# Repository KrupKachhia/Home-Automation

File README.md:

# Home-Automation
The Simple Home Automation System and Door Lock System

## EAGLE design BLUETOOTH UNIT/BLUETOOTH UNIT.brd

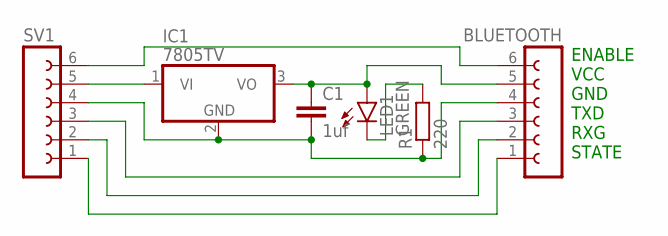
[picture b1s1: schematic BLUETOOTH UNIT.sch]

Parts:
BLUETOOTH: FE06-1; FE06
C1: 1uf; C025-025X050
IC1: 7805TV; TO220V
LED1: GREEN; SML0805
R1: 220; 0204/7
SV1: FE06-1; FE06

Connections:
unnamed: IC1.1 (VI), SV1.5
unnamed: BLUETOOTH.4, C1.2, IC1.2 (GND), R1.1, SV1.4
unnamed: BLUETOOTH.5, C1.1, IC1.3 (VO), LED1.A
unnamed: LED1.C, R1.2
unnamed: BLUETOOTH.3, SV1.3
unnamed: BLUETOOTH.6, SV1.6
unnamed: BLUETOOTH.2, SV1.2
unnamed: BLUETOOTH.1, SV1.1

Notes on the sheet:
ENABLE VCC GND TXD RXG STATE

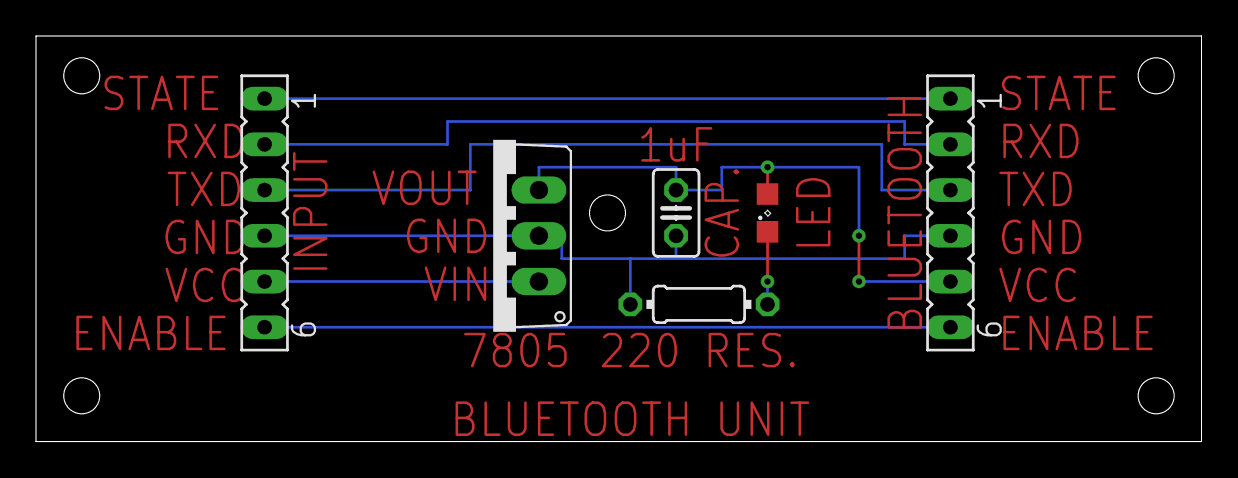
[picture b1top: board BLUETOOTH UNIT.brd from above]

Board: 2 copper layers, 64.8 x 22.5 mm, 6 parts (0 on the bottom side), 8 nets.

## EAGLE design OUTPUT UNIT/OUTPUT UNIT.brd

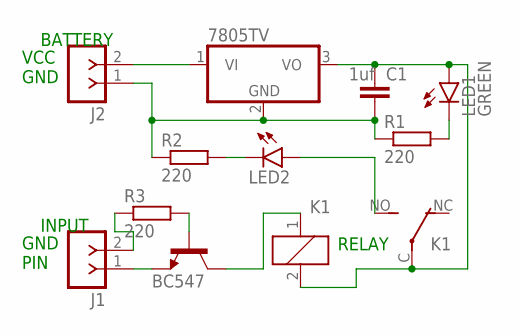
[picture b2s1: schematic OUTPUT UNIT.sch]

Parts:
C1: 1uf; C025-025X050
IC1: 7805TV; TO220V
J1, J2: F-1X02-SIP-100-32Y; SIP-100-02-32Y
K1: CQ1-12V; CQ1
LED1: GREEN; SML1206
LED2: RED; LED5MM
R1, R2, R3: 220; 0204/7
T1: BC547; TO92

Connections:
unnamed: IC1.1 (VI), J2.2
unnamed: J1.1, T1.1 (E)
unnamed: LED1.C, R1.2
unnamed: J1.2, R3.1
unnamed: C1.1, IC1.3 (VO), K1.2, K1.C, LED1.A
unnamed: C1.2, IC1.2 (GND), J2.1, R1.1, R2.1
unnamed: LED2.K (C), R2.2
unnamed: K1.NO (S), LED2.A
unnamed: K1.1, T1.3 (C)
unnamed: R3.2, T1.2 (B)

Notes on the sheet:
BATTERY
INPUT
RELAY
VCC GND
GND PIN

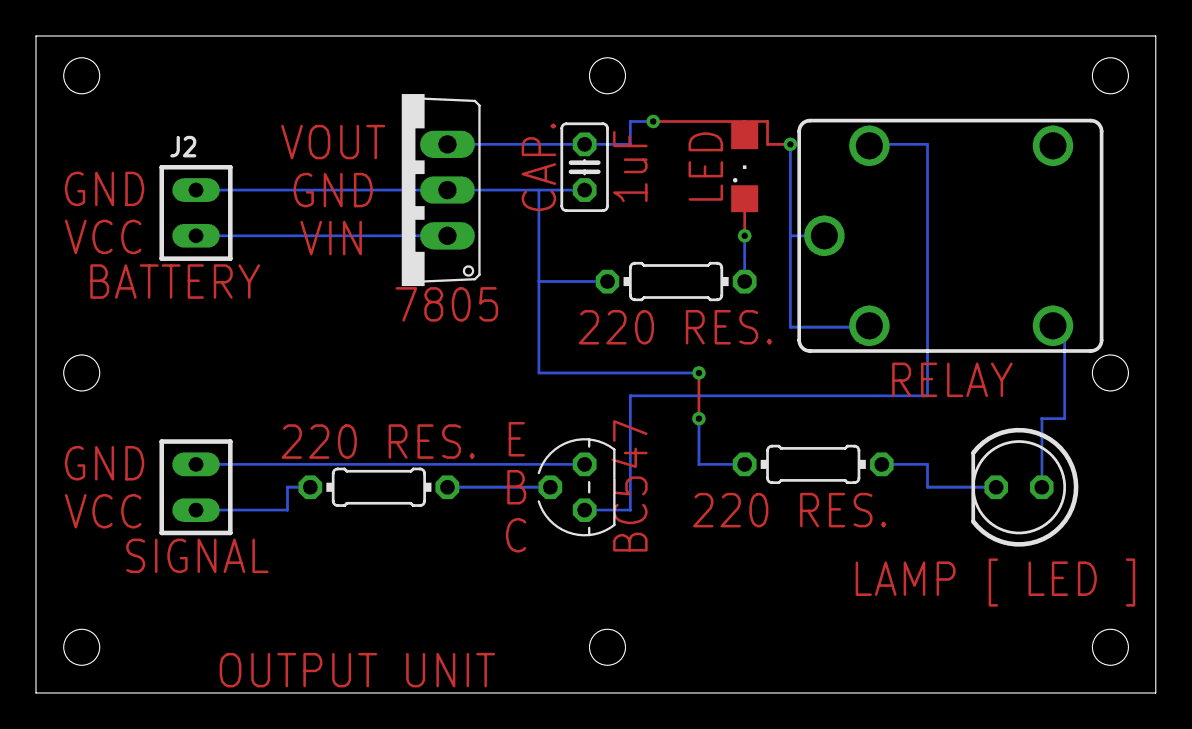
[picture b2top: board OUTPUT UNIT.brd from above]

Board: 2 copper layers, 62.2 x 36.5 mm, 11 parts (0 on the bottom side), 10 nets.

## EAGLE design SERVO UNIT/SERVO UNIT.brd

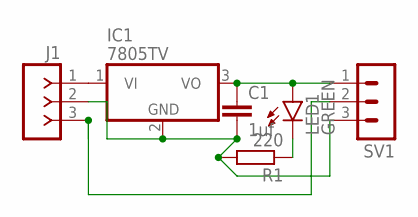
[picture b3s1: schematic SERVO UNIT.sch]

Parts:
C1: 1uf; C025-025X050
IC1: 7805TV; TO220V
J1: F-1X03-SIP-100-32Y; SIP-100-03-32Y
LED1: GREEN; SML0805
R1: 220; 0204/7
SV1: MA03-1

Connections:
unnamed: IC1.1 (VI), J1.1
unnamed: C1.1, IC1.3 (VO), LED1.A, SV1.1
unnamed: LED1.C, R1.1
unnamed: C1.2, IC1.2 (GND), J1.2, R1.2, SV1.3
unnamed: J1.3, SV1.2

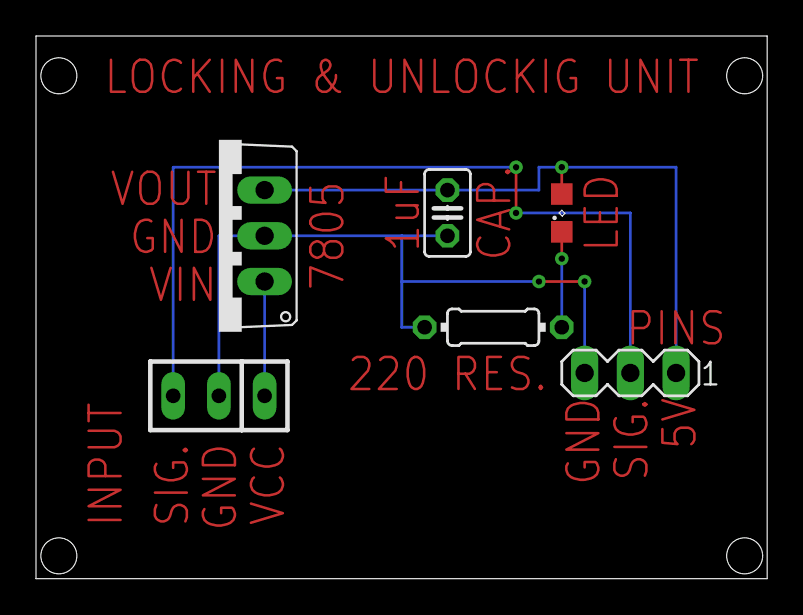
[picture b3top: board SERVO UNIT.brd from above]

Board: 2 copper layers, 40.6 x 30.2 mm, 6 parts (0 on the bottom side), 5 nets.

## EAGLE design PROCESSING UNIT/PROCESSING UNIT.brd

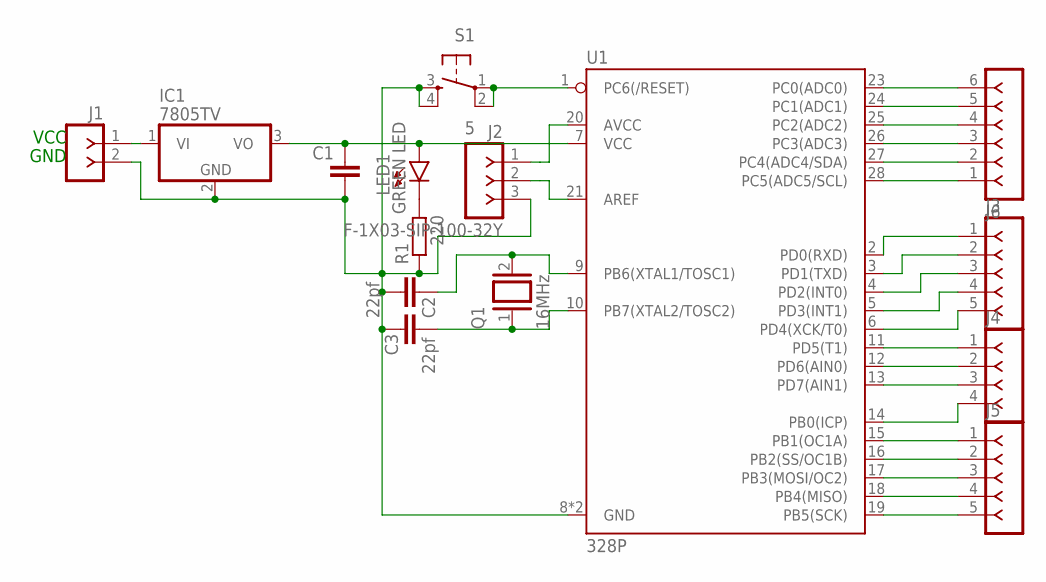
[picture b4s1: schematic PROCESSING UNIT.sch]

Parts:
C1: 1uf; C025-025X050
C2, C3: 22pf; C025-025X050
IC1: 7805TV; TO220V
J1: F-1X02-SIP-100-32Y; SIP-100-02-32Y
J2: F-1X03-SIP-100-32Y; SIP-100-03-32Y
J3, J5: F-1X05-SIP-100-32Y; SIP-100-05-32Y
J4: F-1X04-SIP-100-32Y; SIP-100-04-32Y
J6: F-1X06-SIP-100-32Y; SIP-100-06-32Y
LED1: GREEN LED; SML0603
Q1: 16MHz; QS
R1: 220; 0204/7
S1: 5; TACTILE-PTH
U1: 328P; DIP28

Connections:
unnamed 0: C1.2, C2.1, C3.1, IC1.2 (GND), J1.2, J2.3, R1.1, S1.3, S1.4, U1.8 (GND), U1.22 (GND); also elsewhere on the board
unnamed: S1.1, S1.2, U1.1 (PC6(/RESET))
unnamed: LED1.C, R1.2
unnamed: C2.2, Q1.2, U1.9 (PB6(XTAL1/TOSC1))
unnamed 4: C1.1, IC1.3 (VO), LED1.A, U1.7 (VCC); also elsewhere on the board
unnamed 5: IC1.1 (VI), J1.1; also elsewhere on the board
unnamed: C3.2, Q1.1, U1.10 (PB7(XTAL2/TOSC2))
unnamed: J2.1, U1.20 (AVCC)
unnamed: J2.2, U1.21 (AREF)
unnamed: J3.1, U1.2 (PD0(RXD))
unnamed: J3.2, U1.3 (PD1(TXD))
unnamed: J3.3, U1.4 (PD2(INT0))
unnamed: J3.4, U1.5 (PD3(INT1))
unnamed: J3.5, U1.6 (PD4(XCK/T0))
unnamed: J4.1, U1.11 (PD5(T1))
unnamed: J4.2, U1.12 (PD6(AIN0))
unnamed: J4.3, U1.13 (PD7(AIN1))
unnamed: J4.4, U1.14 (PB0(ICP))
unnamed: J5.1, U1.15 (PB1(OC1A))
unnamed: J5.2, U1.16 (PB2(SS/OC1B))
unnamed: J5.3, U1.17 (PB3(MOSI/OC2))
unnamed: J5.4, U1.18 (PB4(MISO))
unnamed: J5.5, U1.19 (PB5(SCK))
unnamed: J6.1, U1.28 (PC5(ADC5/SCL))
unnamed: J6.2, U1.27 (PC4(ADC4/SDA))
unnamed: J6.3, U1.26 (PC3(ADC3))
unnamed: J6.4, U1.25 (PC2(ADC2))
unnamed: J6.5, U1.24 (PC1(ADC1))
unnamed: J6.6, U1.23 (PC0(ADC0))

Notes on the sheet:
VCC
GND

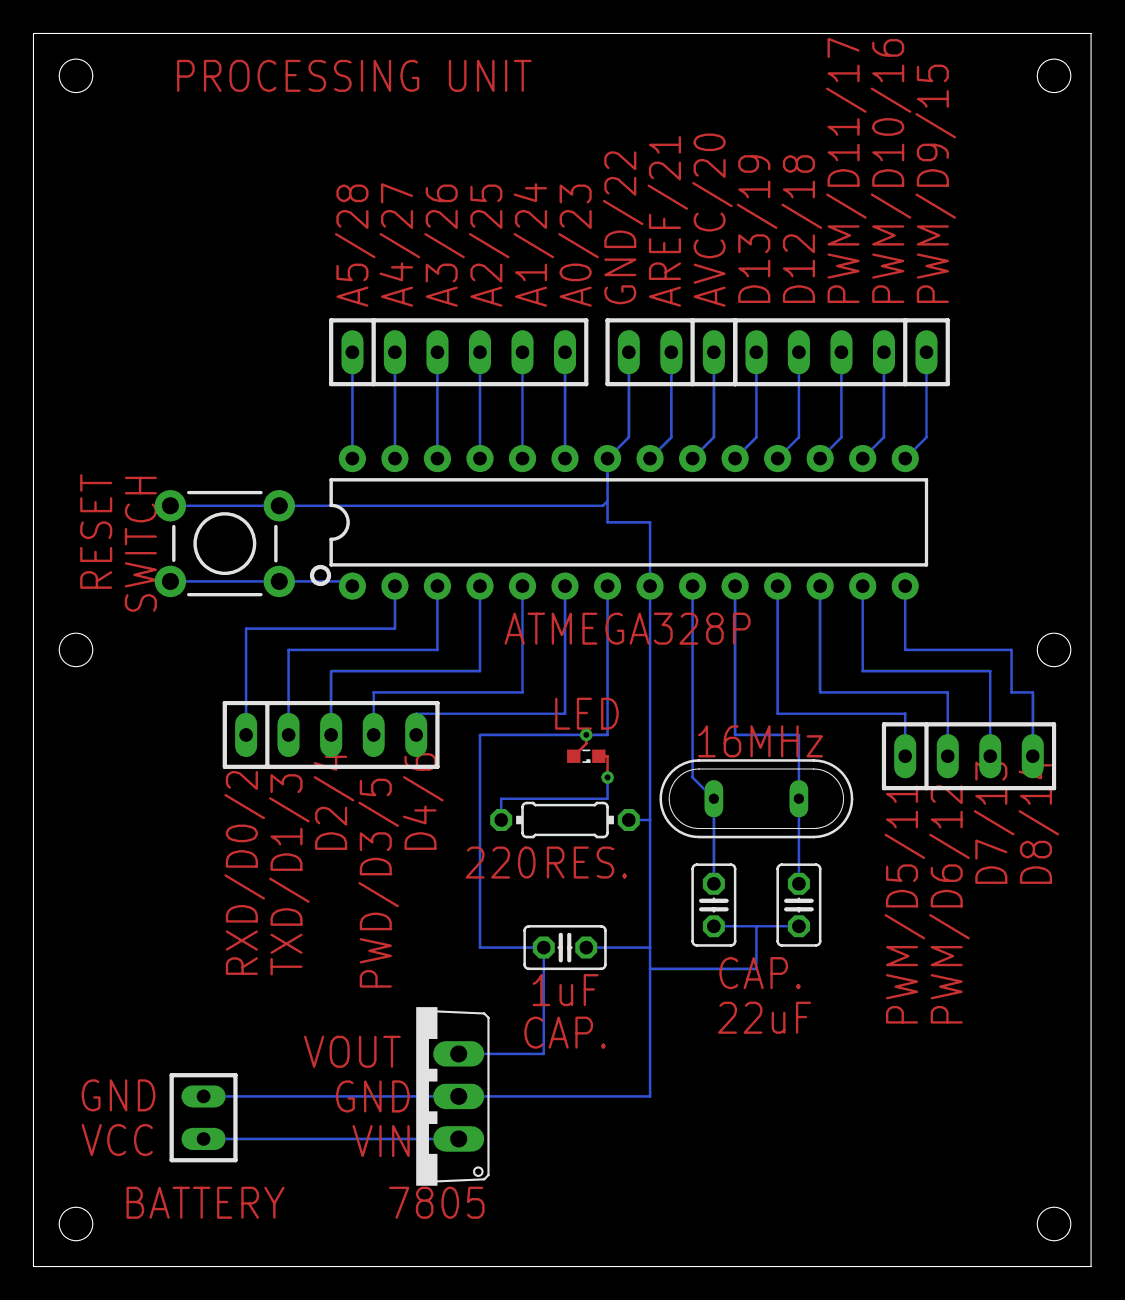
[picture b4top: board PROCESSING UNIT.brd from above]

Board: 2 copper layers, 63.2 x 73.7 mm, 15 parts (0 on the bottom side), 29 nets.

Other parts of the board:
7805: 7805TV; TO220V

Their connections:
unnamed 0: 7805.2; also elsewhere on the board
unnamed 4: 7805.3; also elsewhere on the board
unnamed 5: 7805.1; also elsewhere on the board

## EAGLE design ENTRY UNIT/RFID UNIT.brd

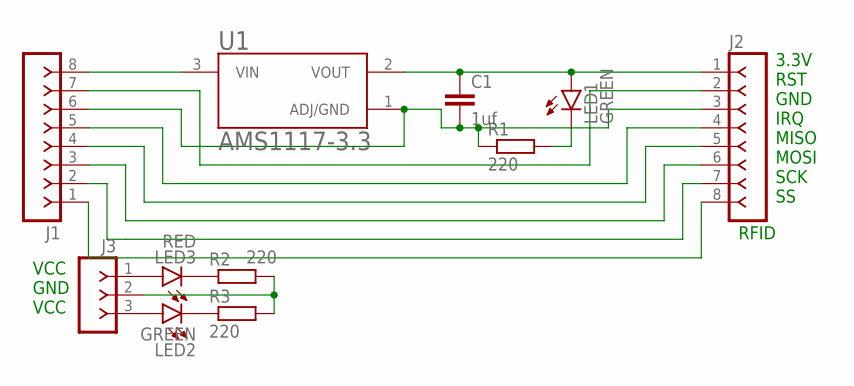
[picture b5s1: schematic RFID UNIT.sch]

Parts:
C1: 1uf; C025-025X050
J1, J2: F-1X08-SIP-100-32Y; SIP-100-08-32Y
J3: F-1X03-SIP-100-32Y; SIP-100-03-32Y
LED1: GREEN; SML0805
LED2: GREEN; LED5MM
LED3: RED; LED5MM
R1, R2, R3: 220; 0204/7
U1: AMS1117-3.3; SOT229P700X180-4N

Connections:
unnamed: C1.1, J2.1, LED1.A, U1.2 (VOUT)
unnamed: J3.3, LED2.A
unnamed: J1.8, U1.3 (VIN)
unnamed: J1.7, J2.2
unnamed: LED3.K (C), R2.1
unnamed: LED2.K (C), R3.1
unnamed: J1.5, J2.4
unnamed: J1.4, J2.5
unnamed: J1.3, J2.6
unnamed: J1.2, J2.7
unnamed: J1.1, J2.8
unnamed: J3.1, LED3.A
unnamed: C1.2, J1.6, J2.3, R1.1, U1.1 (ADJ/GND)
unnamed: J3.2, R2.2, R3.2
unnamed: LED1.C, R1.2

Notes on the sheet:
3.3V RST GND IRQ MISO MOSI SCK SS
RFID
VCC GND VCC

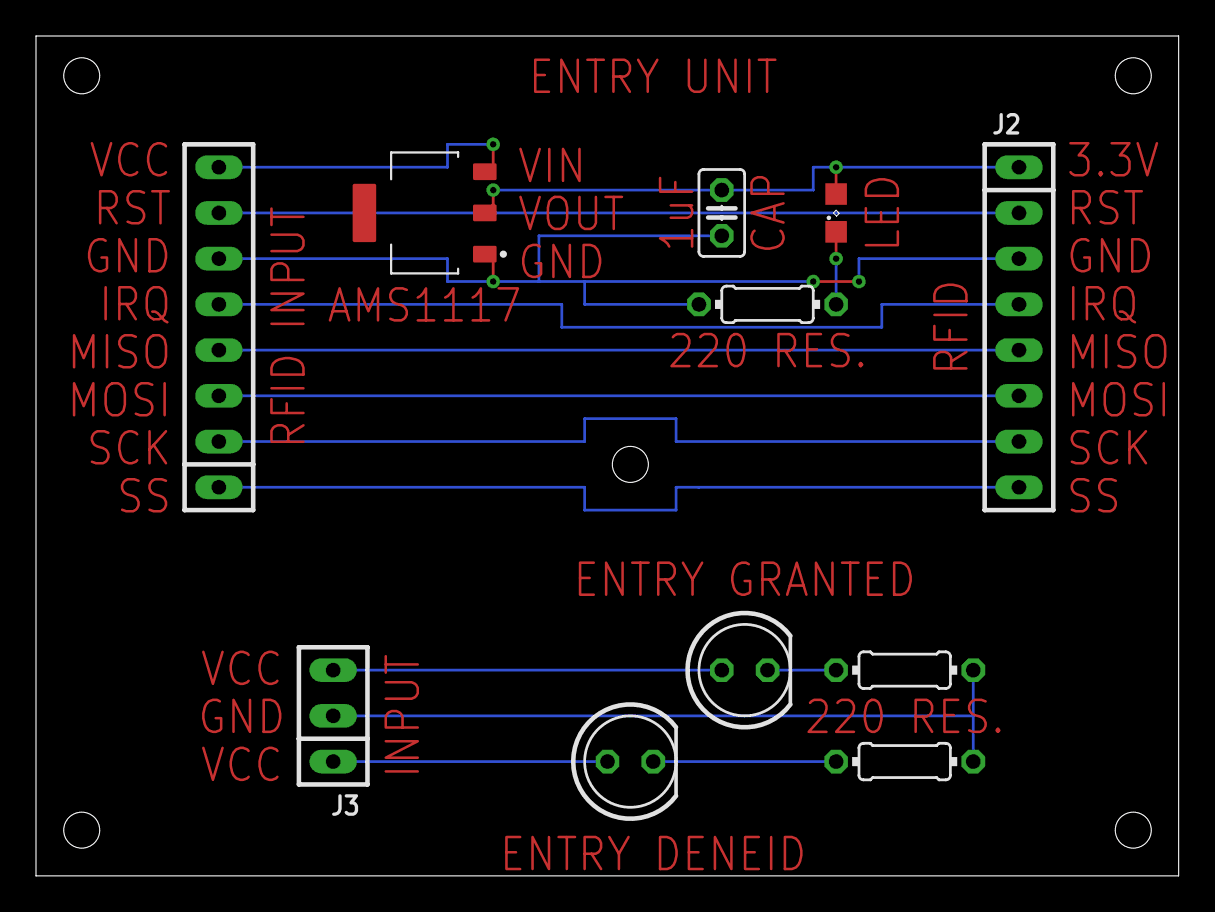
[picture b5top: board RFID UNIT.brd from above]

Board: 2 copper layers, 63.5 x 46.7 mm, 11 parts (0 on the bottom side), 15 nets.

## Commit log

2021-08-30 This is a Simple Home automation System and Door Lock System

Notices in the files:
parts and their libraries:
con-headers-jp: Copyright (C) 2008, Bob Starr
SparkFun-Retired: Licensing: Creative Commons ShareAlike 4.0 International - https://creativecommons.org/licenses/by-sa/4.0
